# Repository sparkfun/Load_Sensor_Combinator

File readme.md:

SparkFun Load Sensor Combinator
=============================

[*SparkFun Load Sensor Combinator (BOB-13281)*](https://www.sparkfun.com/products/13281)

Repository Contents
-------------------
* **/Hardware** - Eagle design files (.brd, .sch)

Documentation
--------------
* **[Hookup Guide](https://learn.sparkfun.com/tutorials/load-cell-amplifier-hx711-breakout-hookup-guideL)** - Basic hookup guide.
* **[SparkFun Fritzing repo](https://github.com/sparkfun/Fritzing_Parts)** - Fritzing diagrams for SparkFun products.
* **[SparkFun 3D Model repo](https://github.com/sparkfun/3D_Models)** - 3D models of SparkFun products. 

How to Use
----------

If you open up an electronic bathroom scale you’ll find a large rats nest of wires. The Load Sensor Combinator was created to combine the 12 wires found in a bathroom scale into the standard 4-wires that wheatstone bridge configuration.

This board also works with four of our individual [load sensors](https://www.sparkfun.com/products/10245). If you aren’t mechanically inclined we recommend purchasing an off-the-shelf bathroom scale and hacking the combinator into it rather than trying to design a base to properly mount four load sensors.

This board works great with our [Load Cell Amplifier](https://www.sparkfun.com/products/13230) breakout board. The five pins on the edge of the combinator line directly up to the five pins on the amplifier.

If your amplifier and supporting electronics are more than a few inches away from the scale an [RJ45 footprint](https://www.sparkfun.com/products/643) is provided. The 4 wheatstone pins (E+/E-/S+/S-) are connected to twisted pairs within a standard cheap ethernet cable. This allows the amplifier board to be placed many feet away from the scale itself.

The combinator board also includes a footprint for the [DS18B20 one wire temperature sensor](https://www.sparkfun.com/products/245). This allows the user to gather the temperature of the scale in case there is a large variance between the scale and the amplifier. These three pins are exposed to the RJ45 connection as well allowing remote temperature readings to be gathered over one twisted pair ethernet cable.

If you plan to use the RJ45 connection you will need to cut and strip the end of the ethernet cable you do not intend to plug into the combinator board. The wires of the exposed ethernet cable connect to the following pins on the combinator board:

* Combinator Pin = Ethernet cable wire color
* E+ = Brown
* E- = Brown white
* NC = Green
* A+ = Blue white
* A- = Blue
* 5V = Green white
* TEMP_DAT = Orange
* GND = Orange white

The NC pin is intentionally left *not connected*. For especially long cables the signals should be shielded against EMI. This is done by using the less common [shielded twisted pair](http://en.wikipedia.org/wiki/Twisted_pair#Cable_shielding) (STP) ethernet cable. The metal foil sheath of the cable creates a telescoping shield by connecting it to ground on the amplifier circuit, not on GND or any other pin on the combinator board.

License Information
-------------------

This product is _**open source**_! 

Please review the LICENSE.md file for license information. 

If you have any questions or concerns on licensing, please contact techsupport@sparkfun.com.

Distributed as-is; no warranty is given.

- Your friends at SparkFun.

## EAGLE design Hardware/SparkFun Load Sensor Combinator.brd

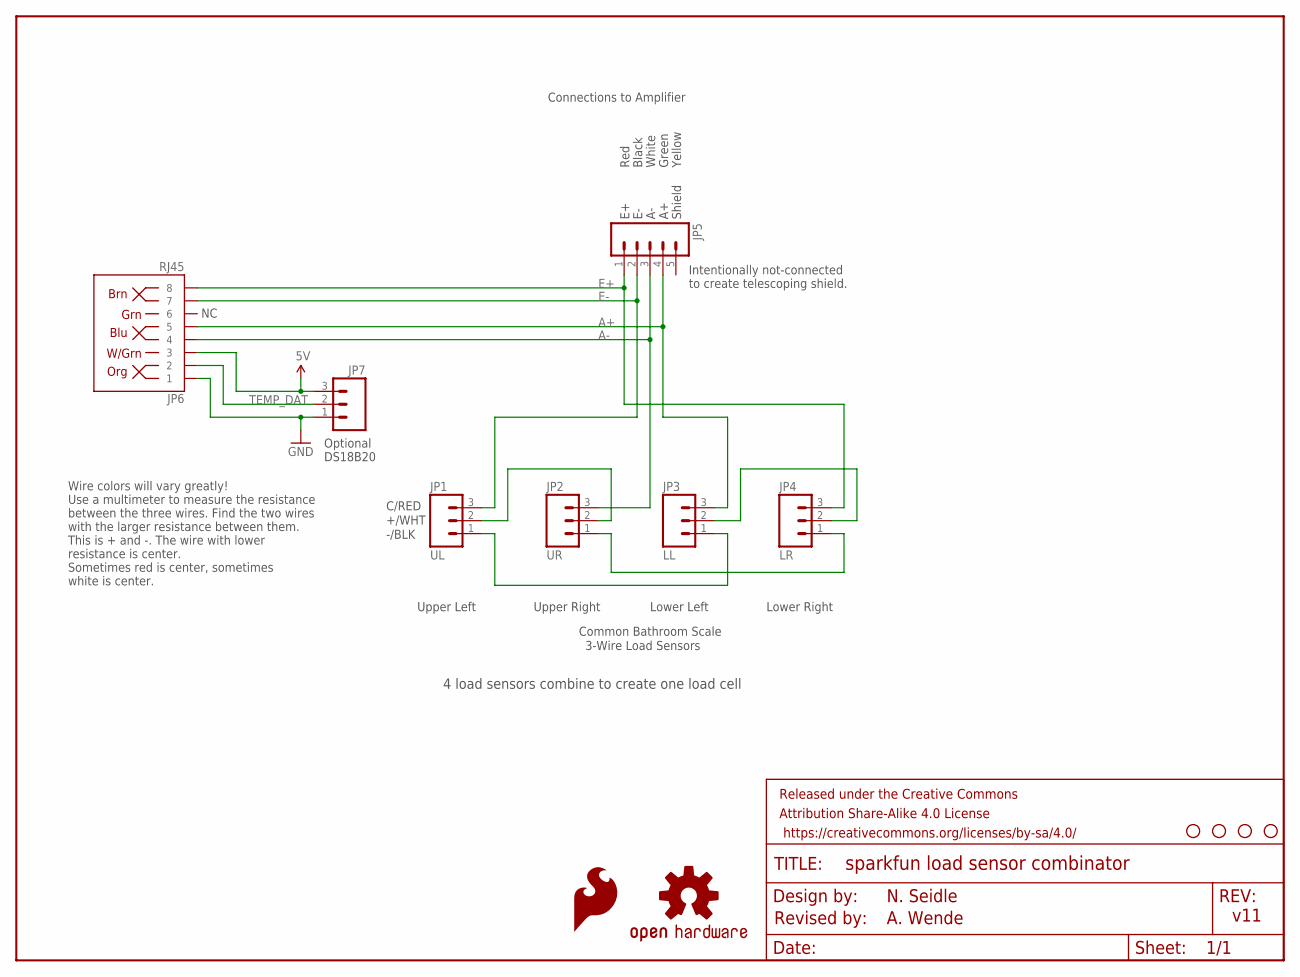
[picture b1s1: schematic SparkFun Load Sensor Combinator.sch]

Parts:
FRAME1: FRAME-LETTER; CREATIVE_COMMONS
JP1: UL; 1X03
JP2: UR; 1X03
JP3: LL; 1X03
JP4: LR; 1X03
JP5: M05PTH; 1X05
JP6: RJ45; RJ45-8
JP7: M03PTH; 1X03
LOGO3: SFE_LOGO_FLAME.1_INCH; SFE_LOGO_FLAME_.1
STANDOFF1, STANDOFF2, STANDOFF3, STANDOFF4: STAND-OFF
U$7: OSHW-LOGOS; OSHW-LOGO-S

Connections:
5V: JP6.3, JP7.3
A+: JP3.3, JP5.4, JP6.5
A-: JP2.3, JP5.3, JP6.4
E+: JP4.3, JP5.1, JP6.8
E-: JP1.3, JP5.2, JP6.7
GND: JP6.1, JP7.1
unnamed: JP2.1, JP4.1
unnamed: JP1.1, JP3.1
unnamed: JP3.2, JP4.2
unnamed: JP1.2, JP2.2
TEMP_DAT: JP6.2, JP7.2

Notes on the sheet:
Red
Black
White
Green
Lower Right
Upper Right
Lower Left
Upper Left
3-Wire Load Sensors
Common Bathroom Scale
Connections to Amplifier
-/BLK
+/WHT
C/RED
4 load sensors combine to create one load cell
Shield
Yellow
Intentionally not-connected to create telescoping shield.
Optional DS18B20
N. Seidle
v11
Revised by:
A. Wende
Wire colors will vary greatly\! Use a multimeter to measure the resistance between the three wires. Find the two wires with the larger resistance between them. This is + and -. The wire with lower resistance is center. Sometimes red is center, sometimes white is center.

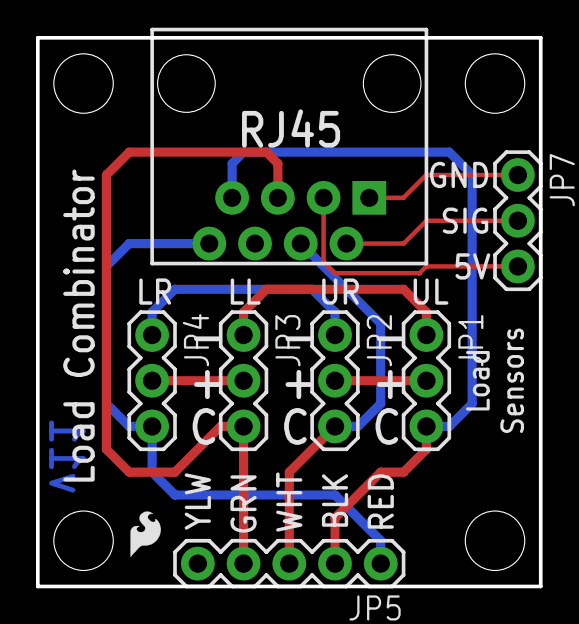
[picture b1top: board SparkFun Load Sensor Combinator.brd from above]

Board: 2 copper layers, 27.9 x 30.5 mm, 14 parts (1 on the bottom side), 11 nets.

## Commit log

2015-01-26 :octocat: Added .gitattributes & .gitignore files
2015-01-26 Added feedback from Eng review
    Match 5-pin connector on breakout. Add yellow pin with NC. Add note to
    schematic describing that 4 sensors create one load cell.
2015-01-26 Added dimensions.
2015-01-30 Added RJ45
2015-01-30 Added dims
2015-01-30 Added DS18S20 connection.
2015-01-30 Correcting name to DS18B20
2015-02-04 Bumped silk and rev 02
    Fixed issue #1
2015-03-25 Fixed a swap between A+ and A-
2015-04-09 Update silk
2015-04-09 Update schematic version
2015-04-10 Adding 5V and GND symbols to schematic.
2015-05-27 Changed silk from BLK to -, WHT to C.
2015-06-10 Updated version on PCB to v11
    v11 changes the silk from R/W/B to more generic and easier to understand
    +/C/-
2015-06-10 Updates to readme with new photos and description
2015-06-10 Readme update
2015-06-10 Readme updates
2015-08-27 Cleaning up repo structure, adding license file
2015-08-27 Reverting Eagle files back to what is being sold on store front
2016-01-21 Added documentation to README
2016-03-21 Revision 11 changes
    Updated labels from R/W/B to +/-/C and moved temp sensor pins down away
    from standoff.

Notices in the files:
parts and their libraries:
SparkFun-Connectors: Licensing: CC v3.0 Share-Alike You are welcome to use this library for commercial purposes.
SparkFun-Aesthetics: Released under the Creative Commons Attribution Share-Alike 4.0 License
SparkFun-Aesthetics: https://creativecommons.org/licenses/by-sa/4.0
